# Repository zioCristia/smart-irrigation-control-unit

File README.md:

# Smart irrigation expansion board
Expansion board for garden irrigation, with 7 differents triacs controlling solenoid valvs and one relay for the water pump.
This board should be attached to the [Esp energy monitor](https://github.com/zioCristia/esp-energy-monitor-v2) board.

You can watch an italian video tutorial throught [this link](https://youtu.be/GwXOpy07zA8).

Should one not need the power monitor, the board could be constructed by eliminating all components related to current measurement, thus leaving only the power supply and esp32.

The board's design allows it to be inserted into the rail of the home's breaker box by printing a 3D component.

The card can be divided into three sub-parts:
* The control of the 24V ac irrigation solenoid valves.
* The control of the water pump (maximum relay 16A).
* The control of the house electric gate from 12V dc.
  
## Table of contents
* [Hardware](#hardware)
* [Software](#software)
* [Pcb](#pcb)
* [Contribution](#contribution)

# Hardware
Each part of the card is independent of the others and can be omitted during construction if there is no need for it.
Similarly, you have the option of controlling 7 irrigation solenoid valves, but you can use a smaller number if you wish.
In this way, the price can vary (in particular reduce) drastically.

A complete list of all the components with a link to aliexpress could be found [here](https://docs.google.com/spreadsheets/d/1A_0oTcwCHzUrwPyKvZikXxDFFEQyVeJslgch1jBqpY8/edit?usp=sharing). The price is very indicative because if you already have components such as resistors or capacitors, it is drastically reduced.

### Additional hardware
For the installation of the board in the house panel directly into standard DIN rails, you can print two clips that you can find on [thingiverse](https://www.thingiverse.com/thing:6103419).

# Software
Esp32 was programmed using EspHome to enable its integration with [Home Assistant](https://www.home-assistant.io). To control solenoid valves, as well as the water pump and gate, simply add the following lines in the EspHome generic code for an esp32.
This will create them as switches in Home Assistant.

For more information, see the example code on the [energy monitor v2](https://github.com/zioCristia/esp-energy-monitor-v2/tree/main#software) or the [EspHome documentation](https://esphome.io).

```
switch:
  - platform: gpio
    name: "Cancello grande interruttore"
    pin: 
      number: GPIO19
      #inverted: true
    id: rele_cancello
    on_turn_on:
    - delay: 500ms
    - switch.turn_off: rele_cancello
    
  - platform: gpio
    pin: GPIO18
    name: "Pompa acqua"
    id: water_pump_switch
    #inverted: true
    restore_mode: ALWAYS_OFF
    
  - platform: gpio
    pin: GPIO15
    name: "irr1"
    id: irr1_switch
    inverted: true
    restore_mode: ALWAYS_OFF
    
  - platform: gpio
    pin: GPIO4
    name: "irr2"
    id: irr2_switch
    inverted: true
    restore_mode: ALWAYS_OFF
    
  - platform: gpio
    pin: GPIO16
    name: "irr3"
    id: irr3_switch
    inverted: true
    restore_mode: ALWAYS_OFF
    
  - platform: gpio
    pin: GPIO17
    name: "irr4"
    id: irr4_switch
    inverted: true
    restore_mode: ALWAYS_OFF
    
  - platform: gpio
    pin: GPIO14
    name: "irr5"
    id: irr5_switch
    inverted: true
    restore_mode: ALWAYS_OFF
    
  - platform: gpio
    pin: GPIO5
    name: "irr7"
    id: irr7_switch
    inverted: true
    restore_mode: ALWAYS_OFF
```

# Pcb
You can find the whole eagle project in [this folder](./irrigation_control_unit).

# Contribution

Feel free to report any bugs or feature requests.

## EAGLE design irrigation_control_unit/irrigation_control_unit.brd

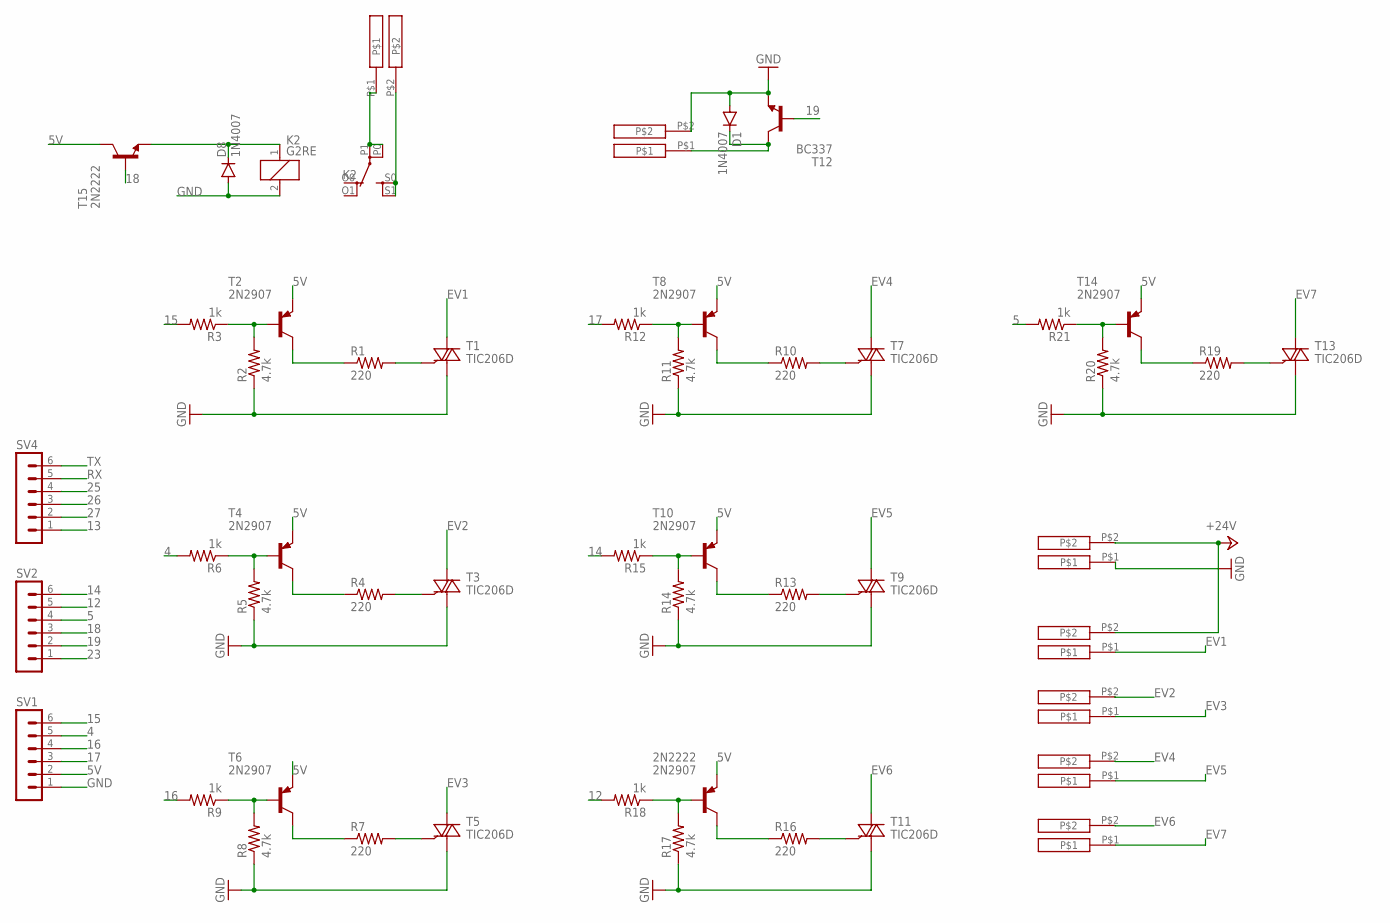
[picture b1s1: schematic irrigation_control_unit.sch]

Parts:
2N2222: 2N2907; TO92-EBC-OVAL
D1, D8: 1N4007; DO35-7
K2: G2RE
R1, R4, R7, R10, R13, R16, R19: 220; 0204/7
R2, R5, R8, R11, R14, R17, R20: 4.7k; 0204/7
R3, R6, R9, R12, R15, R18, R21: 1k; 0204/7
SV1, SV2, SV4: MA06-1
T1, T3, T5, T7, T9, T11, T13: TIC206D; TO220BV
T2, T4, T6, T8, T10, T14: 2N2907; TO92-EBC-OVAL
T12: BC337; TO92
T15: 2N2222; TO92-EBC-OVAL
U$1, U$2, U$3, U$4, U$5, U$6, U$7: 2-PIN-7.5-CONNECTOR

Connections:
4: R6.2, SV1.5
5: R21.2, SV2.4
5V: 2N2222.E, SV1.2, T2.E, T4.E, T6.E, T8.E, T10.E, T14.E, T15.C
12: R18.2, SV2.5
13: SV4.1
14: R15.2, SV2.6
15: R3.2, SV1.6
16: R9.2, SV1.4
17: R12.2, SV1.3
18: SV2.3, T15.B
19: SV2.2, T12.2 (B)
23: SV2.1
25: SV4.4
26: SV4.3
27: SV4.2
+24V: U$1.P$2, U$2.P$2
EV1: T1.T2 (A2), U$2.P$1
EV2: T3.T2 (A2), U$3.P$2
EV3: T5.T2 (A2), U$3.P$1
EV4: T7.T2 (A2), U$4.P$2
EV5: T9.T2 (A2), U$4.P$1
EV6: T11.T2 (A2), U$5.P$2
EV7: T13.T2 (A2), U$5.P$1
GND: D1.A, D8.A, K2.2, R2.1, R5.1, R8.1, R11.1, R14.1, R17.1, R20.1, SV1.1, T1.T1 (A1), T3.T1 (A1), T5.T1 (A1), T7.T1 (A1), T9.T1 (A1), T11.T1 (A1), T12.1 (E), T13.T1 (A1), U$1.P$1, U$7.P$2
unnamed: D8.C, K2.1, T15.E
unnamed: R1.2, T1.G
unnamed: R1.1, T2.C
unnamed: D1.C, T12.3 (C), U$7.P$1
unnamed: R2.2, R3.1, T2.B
unnamed: K2.P0, K2.P1, U$6.P$1
unnamed: K2.S0 (S), K2.S1 (S), U$6.P$2
unnamed: R4.2, T3.G
unnamed: R4.1, T4.C
unnamed: R5.2, R6.1, T4.B
unnamed: R7.2, T5.G
unnamed: R7.1, T6.C
unnamed: R8.2, R9.1, T6.B
unnamed: R10.2, T7.G
unnamed: R10.1, T8.C
unnamed: R11.2, R12.1, T8.B
unnamed: R13.2, T9.G
unnamed: R13.1, T10.C
unnamed: R14.2, R15.1, T10.B
unnamed: R16.2, T11.G
unnamed: 2N2222.C, R16.1
unnamed: 2N2222.B, R17.2, R18.1
unnamed: R19.2, T13.G
unnamed: R19.1, T14.C
unnamed: R20.2, R21.1, T14.B
RX: SV4.5
TX: SV4.6

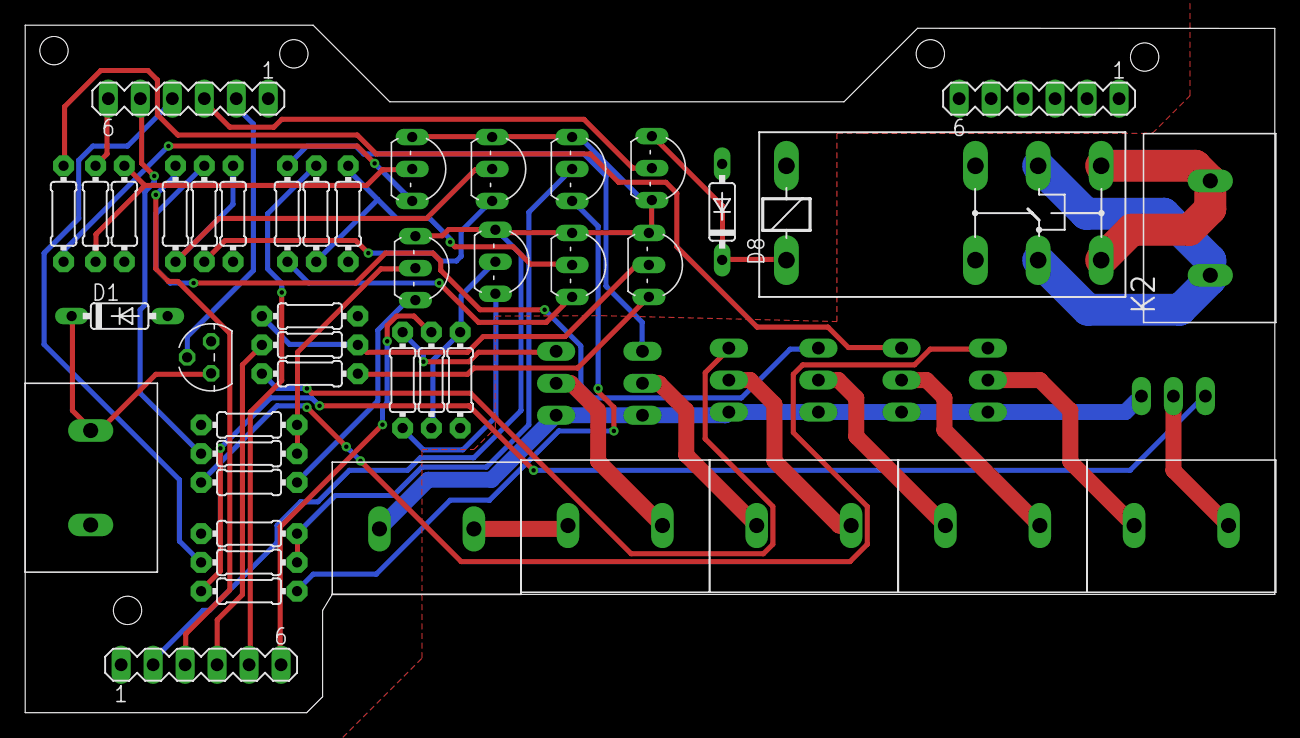
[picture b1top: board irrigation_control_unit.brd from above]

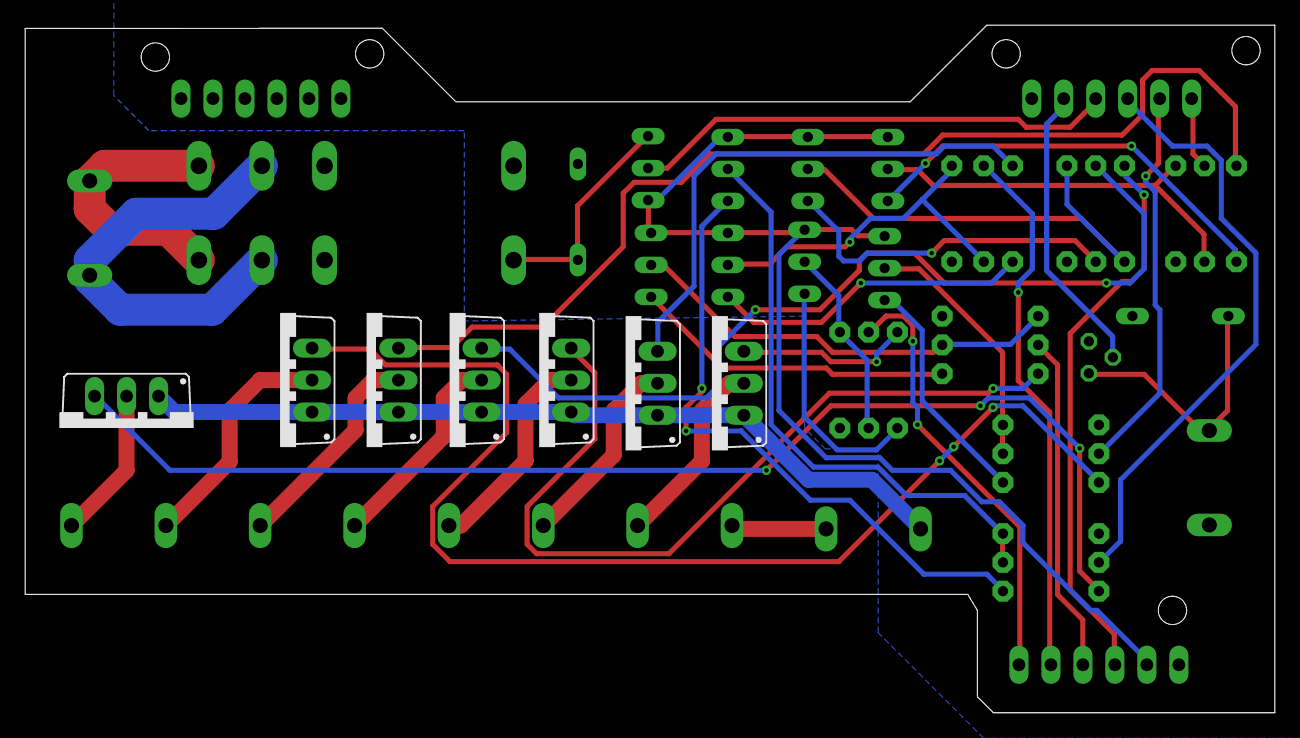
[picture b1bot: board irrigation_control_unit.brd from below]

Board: 2 copper layers, 99.2 x 54.6 mm, 50 parts (7 on the bottom side), 44 nets.

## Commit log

2025-05-25 Create LICENSE
